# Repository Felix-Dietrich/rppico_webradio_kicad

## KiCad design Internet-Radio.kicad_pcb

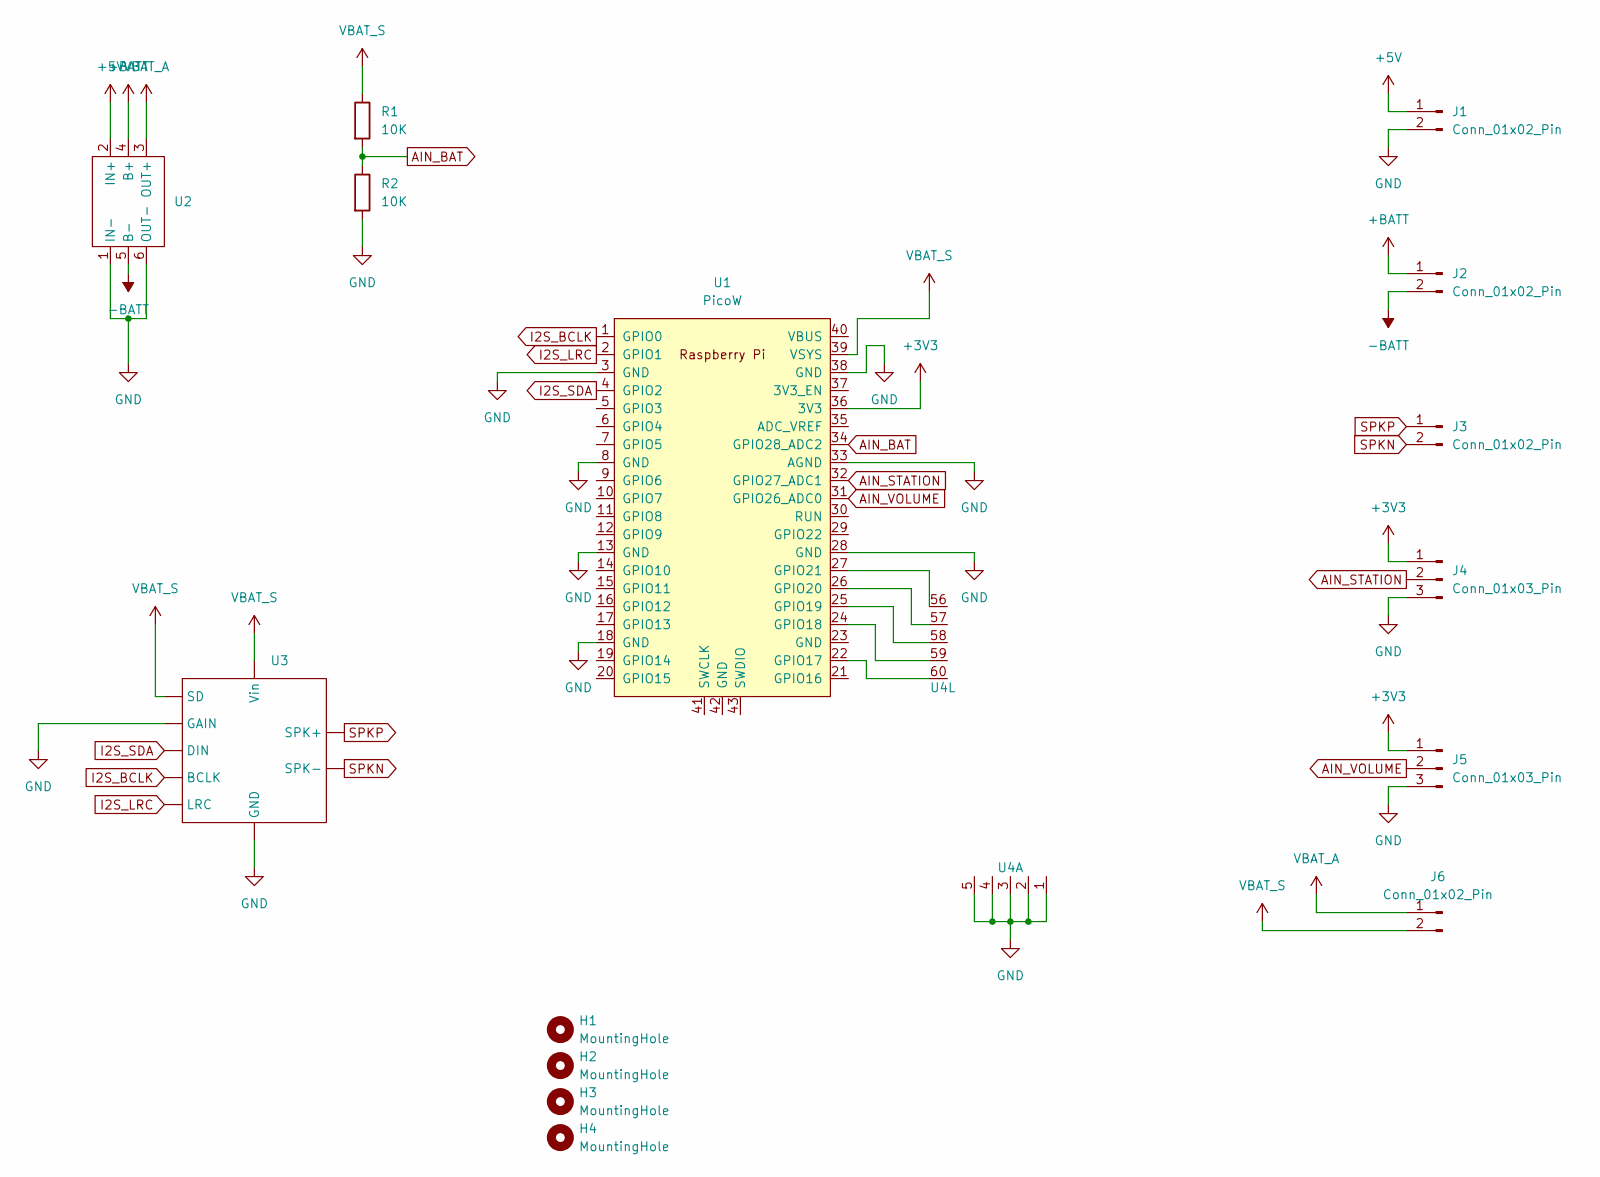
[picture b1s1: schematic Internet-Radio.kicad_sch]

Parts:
H1, H2, H3, H4: MountingHole; MountingHole_3.2mm_M3
J1, J2, J3, J6: Conn_01x02_Pin; PinHeader_1x02_P2.54mm_Vertical
J4, J5: Conn_01x03_Pin; PinHeader_1x03_P2.54mm_Vertical
R1, R2: 10K; R_Axial_DIN0207_L6.3mm_D2.5mm_P10.16mm_Horizontal
U1: PicoW; RPi_PicoW_SMD_TH
U2: BatteryChargeAndProtectionModule
U3: I2SAmplifierModule
U4: Lochraster 5x12

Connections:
+3V3: J4.1, J5.1, U1.36 (3V3)
+5V: J1.1, U2.2 (IN+)
+BATT: J2.1, U2.4 (B+)
-BATT: J2.2, U2.5 (B-)
AIN_BAT: R1.2, R2.1, U1.34 (GPIO28_ADC2)
AIN_STATION: J4.2, U1.32 (GPIO27_ADC1)
AIN_VOLUME: J5.2, U1.31 (GPIO26_ADC0)
GND: J1.2, J4.3, J5.3, R2.2, U1.3 (GND), U1.8 (GND), U1.13 (GND), U1.18 (GND), U1.28 (GND), U1.33 (AGND), U1.38 (GND), U2.1 (IN-), U2.6 (OUT-), U3.2 (GND), U3.4 (GAIN), U4.1, U4.2, U4.3, U4.4, U4.5
I2S_BCLK: U1.1 (GPIO0), U3.6 (BCLK)
I2S_LRC: U1.2 (GPIO1), U3.7 (LRC)
I2S_SDA: U1.4 (GPIO2), U3.5 (DIN)
unnamed: U1.22 (GPIO17), U4.60
unnamed: U1.24 (GPIO18), U4.59
unnamed: U1.25 (GPIO19), U4.58
unnamed: U1.26 (GPIO20), U4.57
unnamed: U1.27 (GPIO21), U4.56
SPKN: J3.2, U3.8 (SPK-)
SPKP: J3.1, U3.9 (SPK+)
V_BAT_A: J6.1, U2.3 (OUT+)
V_BAT_S: J6.2, R1.1, U1.39 (VSYS), U3.1 (Vin), U3.3 (SD)

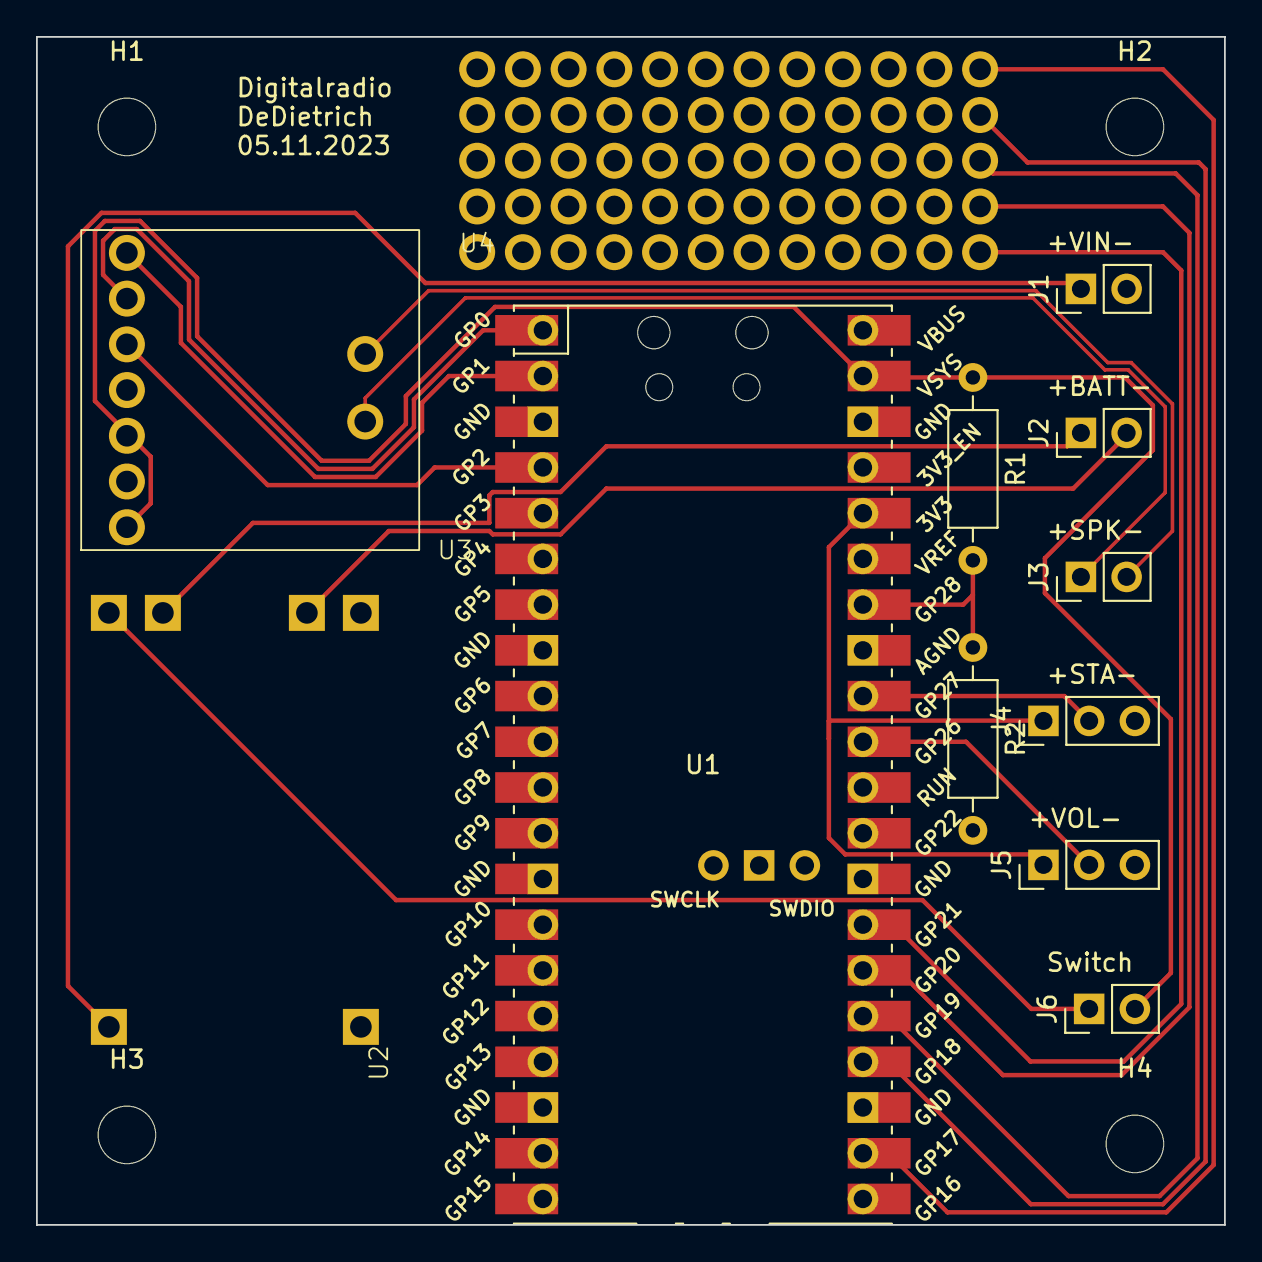
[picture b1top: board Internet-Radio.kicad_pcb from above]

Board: 2 copper layers, 66.0 x 66.0 mm, 16 parts (0 on the bottom side), 20 nets.

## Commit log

2023-12-24 added readme
